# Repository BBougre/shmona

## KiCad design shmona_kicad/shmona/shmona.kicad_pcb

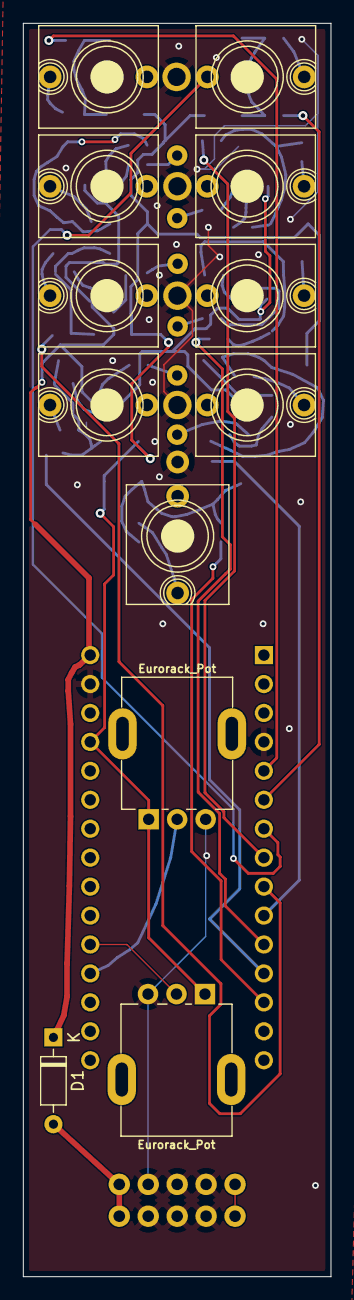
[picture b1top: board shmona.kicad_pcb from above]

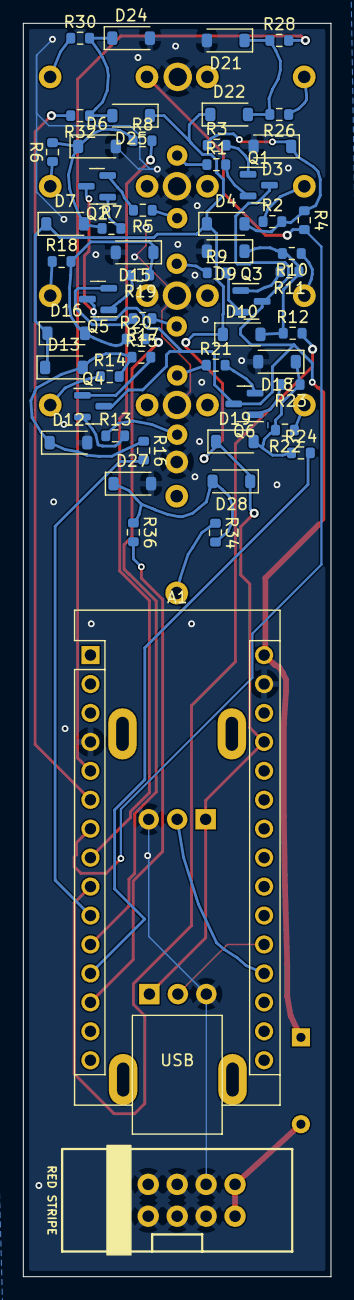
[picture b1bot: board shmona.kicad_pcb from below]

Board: 2 copper layers, 27.0 x 110.0 mm, 74 parts (56 on the bottom side), 51 nets.

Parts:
A1: Arduino_Nano_v3.x; Arduino_Nano
D1: 1N4148; D_DO-35_SOD27_P7.62mm_Horizontal
D2, D5, D8, D11, D14, D17: LED; LED_D3.0mm
D3, D4, D6, D7, D9, D10, D12, D13, D15, D16, D18, D19, D21, D22, D24, D25, D27, D28: D_Schottky; D_SOD-123
J1: Eurorack_Power; Eurorack_Power_2x5_Shrouded
J_1_and_2, J_1_or_2, J_1_xor_2: Eurorack_Mono_Jack; AudioJack_WQP518MA
J_clock_1, J_clock_2: Eurorack_Mono_Jack; AudioJack_WQP518MA
J_out_1, J_out_2, J_out_3: Eurorack_Mono_Jack; AudioJack_WQP518MA
J_reset1: Eurorack_Mono_Jack; AudioJack_WQP518MA
Q1, Q2, Q3, Q4, Q5, Q6: MMBT3904; SOT-23
R1, R2, R4, R5, R6, R8, R9, R10, R12, R13, R14, R16, R17, R18, R20, R21, R22, R24, R30, R32, R34, R36: 470R; R_0603_1608Metric
R3, R7, R11, R15, R19, R23: 10k; R_0603_1608Metric
R26, R28: locked; R_0603_1608Metric
in_Pot_1, in_Pot_2: Eurorack_Pot; Potentiometer_Alpha_R0904N

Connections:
1_and_2: A1.10 (D7), R16.2
1_or_2: A1.11 (D8), R20.2
1_xor_2: A1.12 (D9), R24.2
+5Vo: A1.27 (+5V), D4.1 (K), D7.1 (K), D10.1 (K), D13.1 (K), D16.1 (K), D19.1 (K), D22.1 (K), D25.1 (K), D28.1 (K), in_Pot_1.1, in_Pot_2.1
+12Vo: A1.30 (VIN), D1.1 (K), Q1.3 (C), Q2.3 (C), Q3.3 (C), Q4.3 (C), Q5.3 (C), Q6.3 (C)
GND: A1.4 (GND), A1.29 (GND), D3.2 (A), D6.2 (A), D9.2 (A), D12.2 (A), D15.2 (A), D18.2 (A), D21.2 (A), D24.2 (A), D27.2 (A), J1.3 (GND), J1.4 (GND), J1.5 (GND), J1.6 (GND), J1.7 (GND), J1.8 (GND), J_1_and_2.S (Sleeve), J_1_or_2.S (Sleeve), J_clock_2.S (Sleeve), J_out_2.S (Sleeve), J_reset1.S (Sleeve), in_Pot_1.3, in_Pot_2.3
unnamed: D1.2 (A), J1.9 (+12V), J1.10 (+12V)
unnamed: D2.2 (A), R1.1
unnamed: D3.1 (K), D4.2 (A), R2.2, R3.1, R4.1
unnamed: D5.2 (A), R5.1
unnamed: D6.1 (K), D7.2 (A), R6.2, R7.1, R8.1
unnamed: D8.2 (A), R9.1
unnamed: D9.1 (K), D10.2 (A), R10.2, R11.1, R12.1
unnamed: D11.2 (A), R13.1
unnamed: D12.1 (K), D13.2 (A), R14.2, R15.1, R16.1
unnamed: D14.2 (A), R17.1
unnamed: D15.1 (K), D16.2 (A), R18.2, R19.1, R20.1
unnamed: D17.2 (A), R21.1
unnamed: D18.1 (K), D19.2 (A), R22.2, R23.1, R24.1
unnamed: D21.1 (K), D22.2 (A), R26.2, R28.1
unnamed: D24.1 (K), D25.2 (A), R30.2, R32.1
unnamed: D27.1 (K), D28.2 (A), R34.2, R36.1
unnamed: J_1_and_2.T (Tip), R14.1
unnamed: J_1_or_2.T (Tip), R18.1
unnamed: J_1_xor_2.T (Tip), R22.1
unnamed: J_clock_1.T (Tip), R26.1
unnamed: J_clock_2.T (Tip), R30.1
unnamed: J_out_1.T (Tip), R2.1
unnamed: J_out_2.T (Tip), R6.1
unnamed: J_out_3.T (Tip), R10.1
unnamed: J_reset1.T (Tip), R34.1
unnamed: Q1.1 (B), R3.2
unnamed: Q1.2 (E), R1.2
unnamed: Q2.1 (B), R7.2
unnamed: Q2.2 (E), R5.2
unnamed: Q3.1 (B), R11.2
unnamed: Q3.2 (E), R9.2
unnamed: Q4.1 (B), R15.2
unnamed: Q4.2 (E), R13.2
unnamed: Q5.1 (B), R19.2
unnamed: Q5.2 (E), R17.2
unnamed: Q6.1 (B), R23.2
unnamed: Q6.2 (E), R21.2
clock_1: A1.5 (D2), R28.2
clock_2: A1.6 (D3), R32.2
out_1: A1.7 (D4), J_clock_2.TN (Tip_normalize), R4.2
out_2: A1.8 (D5), R8.2
out_3: A1.9 (D6), R12.2
pot_1: A1.19 (A0), in_Pot_1.2
pot_2: A1.20 (A1), in_Pot_2.2
reset: A1.13 (D10), R36.2

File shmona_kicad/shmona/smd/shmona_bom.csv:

Comment,Designator,Footprint,LCSC
D_Schottky,"D3, D4, D6, D7, D9, D10, D12, D13, D15, D16, D18, D19, D21, D22, D24, D25, D27, D28",Diode_SMD:D_SOD-123,C8598
MMBT3904,"Q1, Q2, Q3, Q4, Q5, Q6",Package_TO_SOT_SMD:SOT-23,C20526
470R,"R1, R2, R4, R5, R6, R8, R9, R10, R12, R13, R14, R16, R17, R18, R20, R21, R22, R24, R26, R28, R30, R32, R34, R36",Resistor_SMD:R_0603_1608Metric,C23179
10k,"R3, R7, R11, R15, R19, R23",Resistor_SMD:R_0603_1608Metric,C25804

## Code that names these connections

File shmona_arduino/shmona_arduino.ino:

#include <TimerOne.h>
#include "TABLE_EIGHT.h"


#define clck_1 2
#define clck_2 3
#define out_1 4 // 16 0b00010000 on PORTD 
#define out_2 5 // 32 0b00100000 on PORTD
#define out_3 6
#define out_and 9
#define out_or 8
#define out_xor 7
#define reset 10
 
#define in_pot_1 A0
#define in_pot_2 A1

const uint16_t tempo = 100;

volatile uint16_t pot_1 = 0;
volatile uint16_t pot_2 = 0;

volatile uint16_t rythm_1 = 0;
volatile uint16_t rythm_2 = 0;
volatile uint16_t rythm_3 = 0;

volatile bool step_done_1 = false;
volatile bool step_done_2 = false;
volatile bool step_done_3 = false;
volatile bool reset_done = false;

volatile uint8_t step_count_1 = 1;
volatile uint8_t step_count_2 = 1;
volatile uint16_t step_count_3 = 1;


volatile uint8_t one_OR_two = 0;
volatile uint8_t one_AND_two = 0;
volatile uint8_t one_XOR_two = 0;



void setup() {
	// setup serial
	//Serial.begin(9600);           
	// Setup PINs
	pinMode(clck_1, INPUT_PULLUP);
	pinMode(clck_2, INPUT_PULLUP);
	pinMode(reset, INPUT);
	pinMode(out_1, OUTPUT);
  	pinMode(out_2, OUTPUT);
	pinMode(out_3, OUTPUT);	
	
	pinMode(out_and, OUTPUT);
	pinMode(out_xor, OUTPUT);
	pinMode(out_or, OUTPUT);

	pinMode(reset, INPUT_PULLUP);
	
//	Timer stuff
	Timer1.initialize(tempo);
	Timer1.attachInterrupt(check_all);
	Timer1.start();
	//Serial.println("There it goes");
	delay(1000);	
}

void loop() {

}

void check_all() {
	read_pots();
	do_reset();
	do_rythm_1();
	do_rythm_2();
	do_logic();
	// add reset here
}

void do_reset() {
	if (digitalRead(reset) & ! reset_done) {
		step_count_1 = 1;
		step_count_2 = 1;
		step_count_3 = 1;
		reset_done = true;
	}
	if (! digitalRead(reset) & reset_done) {
		reset_done = false;
	}
}

uint16_t do_mixing(uint8_t in_1, uint8_t in_2, uint8_t half = 8) {
	// with 0b11001 and 0b01101 should output 0b0111100011
	uint16_t mixed = 0;
	uint16_t j = 0;
    	uint16_t maskos = 0b1;
      
	for (uint8_t i = 0; i < half; i++) {
		mixed |= ((in_1 & (maskos << i)) > 0) << j;
		j += 1;
		mixed |= ((in_2 & (maskos << i)) > 0) << j;
		j += 1;
	}
	return mixed;
}

void read_pots() {
	pot_1 = 255 - (analogRead(in_pot_1) >> 2);
	pot_2 = 255 - (analogRead(in_pot_2) >> 2);
}

void do_rythm_1() {		
	rythm_1 = uint8_t pgm_read_word(&(table_eight[pot_1]));
	
	if (digitalRead(clck_1) == HIGH && step_done_1 == false) {
		/* rythm 1 */
		digitalWrite(out_1, (rythm_1 & step_count_1) > 0);
		//Serial.print("step : ");Serial.print(step_count_1);Serial.print("\t");Serial.println(step_count_1, BIN);
		//Serial.print("rythm_1: ");Serial.print(rythm_1, BIN); Serial.print(" ||| "); Serial.println(rythm_1);
		step_count_1 *=2;
		if (step_count_1 == 0) step_count_1 = 1;
		
		/* rythm 3 */
		rythm_3 = do_mixing(rythm_1, rythm_2);
		digitalWrite(out_3, (rythm_3 & step_count_3) > 0);
		//Serial.print("step : ");Serial.print(step_count_3);Serial.print("\t");
		//Serial.println(step_count_3, BIN);
		//Serial.print("rythm_3: "); Serial.print(rythm_3, BIN); Serial.print("|||"); Serial.println(rythm_3);		
		step_count_3 *=2;
		if (step_count_3 == 0) step_count_3 = 1;		
		step_done_1 = true;
		
	} else if (digitalRead(clck_1) == LOW && step_done_1 == true) {
		step_done_1 = false;
		digitalWrite(out_1, 0);
		digitalWrite(out_3, 0);
	}
}

void do_rythm_2() {

	
	rythm_2 = uint8_t pgm_read_word_near(&(table_eight[pot_2]));			
	if (digitalRead(clck_2) == HIGH && step_done_2 == false) {
		digitalWrite(out_2, rythm_2 & step_count_2);
		//Serial.print("rythm_2: ");Serial.print(rythm_2, BIN); Serial.print(" ||| "); Serial.println(rythm_2);
		//Serial.print("step : ");Serial.print(step_count_2);Serial.print("\t");Serial.println(step_count_2, BIN);
		step_count_2 *=2;
		if (step_count_2 == 0) step_count_2 = 1;
		step_done_2 = true;	
	} else if (digitalRead(clck_2) == LOW && step_done_2 == true) {
		step_done_2 = false;
		digitalWrite(out_2, 0);
	}
}

void do_logic() {
	one_OR_two =  (PORTD & 16) || (PORTD & 32);
	one_AND_two = (PORTD & 16) && (PORTD & 32);
	//Serial.print(one_OR_two); 	Serial.print("\t");Serial.println(one_AND_two);	
     //Serial.println(one_OR_two && (!one_AND_two));
	digitalWrite(out_or,  one_OR_two);
	digitalWrite(out_and,  one_AND_two);
	digitalWrite(out_xor, one_OR_two && !(one_AND_two));	
}

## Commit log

2024-03-13 added all code data
2024-03-13 kicad schematics data added
